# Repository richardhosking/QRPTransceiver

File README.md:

# QRPTransceiver

QRPTransceiver is an HF transceiver project using phasing techniques, surface-mount components, KiCad hardware design files, and Raspberry Pi Pico firmware for control and user interface.

## Overview

The repository combines:

- **hardware design** in KiCad
- **firmware** for Raspberry Pi Pico using PlatformIO/Arduino
- **local oscillator control** using an SI5351
- **front-panel UI** using a rotary encoder, push buttons, and an ILI9341 TFT display

The design is centered on a phasing-based architecture for HF operation and is being developed as an integrated hardware/firmware system.

## Repository Structure

```text
.
├── firmware/
│   ├── src/                # Main firmware application
│   ├── lib/                # Firmware libraries (UI, input, SI5351 control, etc.)
│   ├── include/            # Shared firmware headers
│   ├── test/               # Firmware tests
│   ├── scripts/            # Utility scripts
│   └── platformio.ini      # PlatformIO project file
├── hardware/
│   ├── kicad/
│   │   ├── QRPTransceiver.kicad_pro
│   │   ├── QRPTransceiver.kicad_sch
│   │   ├── QRPTransceiver.kicad_pcb
│   │   ├── QRPTransceiver.pretty/   # Local footprint library
│   │   └── lib_sch/                 # Local symbol library files
│   └── outputs/            # Manufacturing outputs, exports, and generated artifacts
├── docs/
│   ├── architecture.md
│   ├── bringup.md
│   ├── calibration.md
│   ├── firmware-overview.md
│   ├── hardware-overview.md
│   ├── pinout.md
│   └── summaries/          # Summary notes and rework history
├── reference/
│   ├── datasheets/         # Reference component datasheets
│   └── licenses/           # License/reference documents
├── archive/
│   ├── backups/            # Backup zips, cache/rescue files, and *-bak artifacts
│   ├── legacy-kicad/       # Legacy KiCad schematic/netlist files
│   └── temporary/          # Autosave, lock, and temporary design files
└── README.md
```

The repository is now organized so that active firmware lives under `firmware/`, the active KiCad project lives under `hardware/kicad/`, generated hardware outputs live under `hardware/outputs/`, and reference material is stored under `reference/`.

## Main Subsystems

### Hardware
- main transceiver schematic and PCB
- hierarchical sheets for mixer, polyphase, and receiver audio sections
- local symbol and footprint libraries
- manufacturing outputs and design reports

### Firmware
- `firmware/src/main.cpp` as the control entry point
- `firmware/lib/DisplayUI` for the TFT display layer
- `firmware/lib/RotaryInput` for tuning encoder input
- `firmware/lib/PushButtons` for front-panel button handling
- `firmware/lib/SI5351Control` for synthesizer control and band-specific quadrature setup

## Documentation

Project documentation is organized under `docs/`:

- `docs/architecture.md` — overall system architecture
- `docs/bringup.md` — bring-up notes and observations
- `docs/calibration.md` — calibration workflow and notes
- `docs/hardware-overview.md` — hardware design structure and subsystem roles
- `docs/firmware-overview.md` — firmware organization and responsibilities
- `docs/pinout.md` — firmware-visible pin assignments
- `docs/summaries/` — summary notes for key refactors, programming flow, and quadrature correction work

## Current Status

The repository currently contains:
- active KiCad project files under `hardware/kicad/`
- firmware for Pico-based control and display under `firmware/`
- generated outputs under `hardware/outputs/`
- reference materials under `reference/`
- archived legacy, backup, and intermediate design artifacts under `archive/`

As the project evolves, the active KiCad project and PlatformIO firmware remain the primary editable sources in their dedicated subdirectories.

## Toolchain

### Hardware
- KiCad 8 project files are present under `hardware/kicad/`

### Firmware
- PlatformIO
- Arduino framework for Raspberry Pi Pico
- SI5351 library
- Adafruit GFX / ILI9341 display libraries

## Notes

This project is an active mixed-domain design spanning:

- RF/analog circuit design
- phasing-based transceiver architecture
- embedded firmware
- user interface development
- calibration and layout refinement

For architectural details, start with `docs/architecture.md`.

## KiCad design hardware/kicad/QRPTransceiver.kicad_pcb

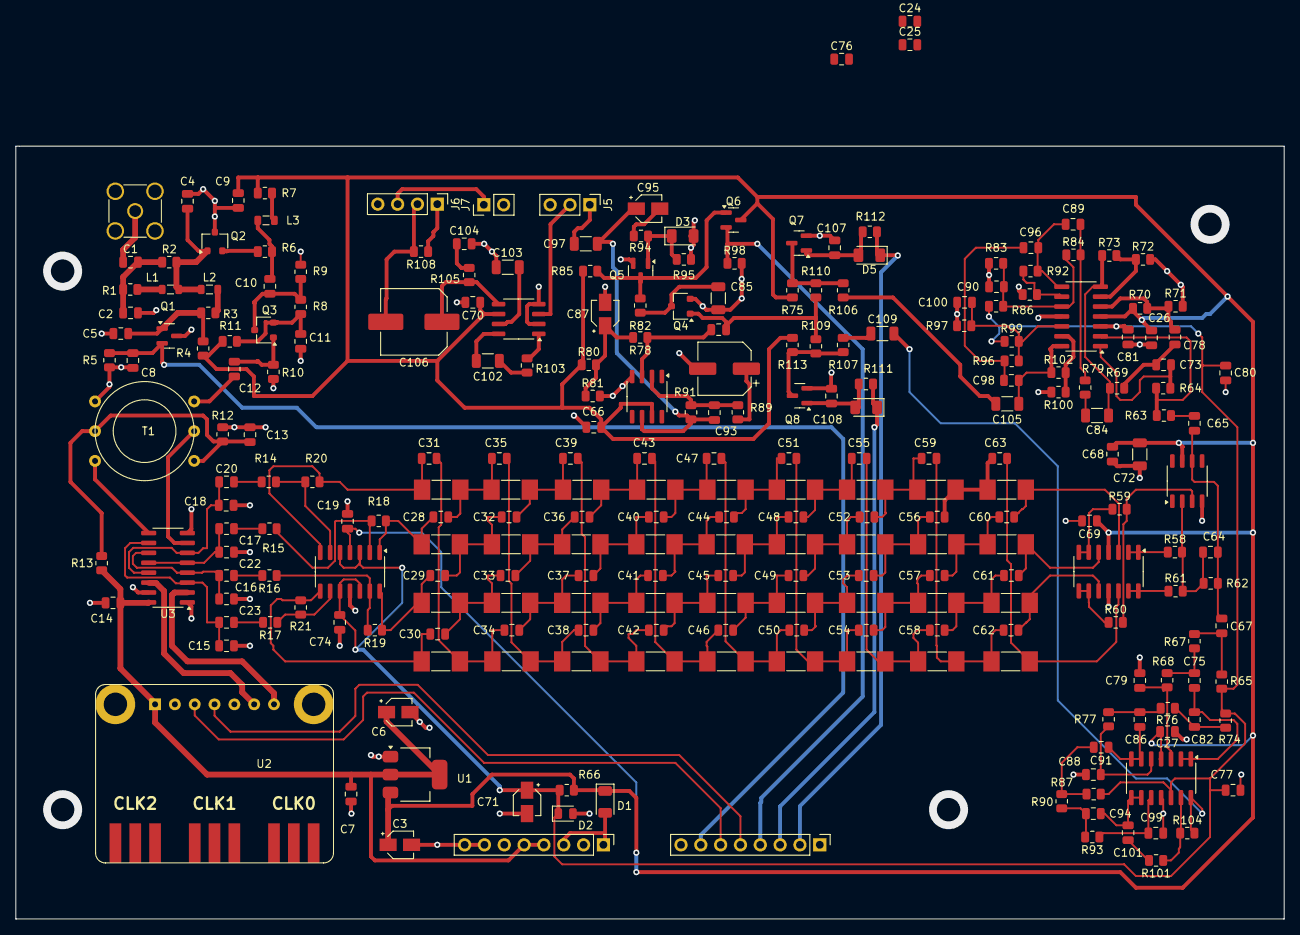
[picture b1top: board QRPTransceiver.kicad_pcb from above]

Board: 2 copper layers, 162.5 x 99.0 mm, 255 parts (0 on the bottom side), 146 nets.

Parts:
C1, C28, C29, C30, C31, C32, C33, C34, C35, C36, C37, C38, C39, C40, C41, C42, C43, C44, C45, C46, C47, C48, C49, C50, C51, C52, C53, C54, C55, C56, C57, C58, C59, C60, C61, C62, C63, C89, C90, C96, C98, C100: 10n; C_0805_2012Metric
C2, C4, C12: 1n; C_0805_2012Metric
C3, C6, C87, C95: 10u; CP_Elec_3x5.3
C5, C7, C8, C9, C10, C11, C13, C14, C19, C24, C25, C26, C27, C65, C66, C67, C68, C69, C70, C73, C74, C76, C77, C78, C80, C81, C83, C101, C107, C108: 100n; C_0805_2012Metric
C15, C16, C17, C18: 470n; C_0805_2012Metric
C20, C21, C22, C23: 220n; C_0805_2012Metric
C64, C79: 220p; C_0805_2012Metric
C71: 47u; CP_Elec_3x5.3
C72, C102, C103: 10u; C_1206_3216Metric
C75, C82, C91, C104: 47n; C_0805_2012Metric
C84, C85, C97, C105, C109: 1u; C_1206_3216Metric
C86, C94: 33n; C_0805_2012Metric
C88, C99: 470p; C_0805_2012Metric
C92: 47u; CP_Elec_6.3x4.9
C93: 33p; C_0805_2012Metric
C106: 220u; C_Elec_8x10.2
D1: IN4001; D_1206_3216Metric
D2: 6V2; D_0805_2012Metric
D3: 1N4142; D_1206_3216Metric
D4, D5: 1N914; D_1206_3216Metric
J1: Data; PinHeader_1x08_P2.54mm_Vertical
J2: Power; PinHeader_1x08_P2.54mm_Vertical
J3: Input; SMA_Amphenol_901-144_Vertical
J5: Audio Gain; PinHeader_1x03_P2.54mm_Vertical
J6: Audio Out; PinHeader_1x04_P2.54mm_Vertical
J7: Speaker; PinHeader_1x02_P2.54mm_Vertical
L1: 100n; L_0805_2012Metric
L2: 1n; L_0805_2012Metric
L3: 500u; L_0805_2012Metric
Q1: VN10N; SOT-23
Q2, Q3: 2SK2394; SC-59
Q4: J177; SC-59
Q5, Q6: 2N3904; SOT-23
Q7, Q8: VN10LF; SOT-23
R1, R3: 47; R_0805_2012Metric
R2: 100; R_0805_2012Metric
R4, R5, R10, R13, R18, R19, R20, R21, R58, R59, R60, R61, R69, R71, R73, R75, R85, R94, R98, R101, R106, R107, R113: 10K; R_0805_2012Metric
R6, R7, R14, R15, R16, R17, R82, R111, R112: 1K; R_0805_2012Metric
R8, R9, R65, R74, R78, R83, R87: 1M; R_0805_2012Metric
R11: 10; R_0805_2012Metric
R12: 6K8; R_0805_2012Metric
R22, R23, R24, R25: 3K3; R_MELF_MMB-0207
R26, R27, R28, R29: 4K7; R_MELF_MMB-0207
R30, R31, R32, R33: 6K8; R_MELF_MMB-0207
R34, R35, R36, R37: 10K; R_MELF_MMB-0207
R38, R39, R40, R41: 15K; R_MELF_MMB-0207
R42, R43, R44, R45: 22K; R_MELF_MMB-0207
R46, R47, R48, R49: 33K; R_MELF_MMB-0207
R50, R51, R52, R53: 47K; R_MELF_MMB-0207
R54, R55, R56, R57: 68K; R_MELF_MMB-0207
R62, R91: 220K; R_0805_2012Metric
R63: 22K; R_0805_2012Metric
R64, R95, R102: 47K; R_0805_2012Metric
R66, R79, R84: 4K7; R_0805_2012Metric
R67, R68, R72: 33K; R_0805_2012Metric
R70, R92: 18K; R_0805_2012Metric
R76, R77, R90, R93: 56K; R_0805_2012Metric
R80, R81, R109, R110: 100K; R_0805_2012Metric
R86, R99: 470K; R_0805_2012Metric
R88, R100: 39K; R_0805_2012Metric
R89, R96: 3K3; R_0805_2012Metric
R97: 390K; R_0805_2012Metric
R103: 1K2; R_0805_2012Metric
R104: 27K; R_0805_2012Metric
R105: 10R; R_0805_2012Metric
R108: 470R; R_0805_2012Metric
T1: Input; T50-2TrifilarTransformer
U1: AP1117-50; SOT-223-3_TabPin2
U2: Si5351Module
U3: FST3253; SOIC-16_3.9x9.9mm_P1.27mm
U4, U5, U7, U8: TS924; SO-14_3.9x8.65mm_P1.27mm
U6, U9: OPA1641; SO-8_3.9x4.9mm_P1.27mm
U10: LM386; SO-8_3.9x4.9mm_P1.27mm

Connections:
+5V: C6.1, C7.1, C14.1, J2.4, J2.5, R13.1, U1.2 (VO), U2.1 (VCC), U3.16 (VCC)
+12V: C3.1, C9.1, C19.1, C24.1, C25.1, C26.1, C27.1, C66.1, C68.1, C69.1, C70.1, C72.1, C76.1, D1.1 (K), Q6.3, R4.2, R7.2, R11.2, R66.1, R70.2, R75.1, R80.1, R85.1, R113.1, U1.3 (VI), U4.4 (V+), U5.4 (V+), U6.7 (V+), U7.4 (V+), U8.4 (V+), U9.7 (V+), U10.6 (V+)
/Sheet6280C94B/AudioAGC: C83.1, Q4.1 (D), R109.1, R110.1
/Sheet62579414/A: C31.2, R20.1, R22.2, U4.7
/Sheet62579414/B: C28.1, C35.2, R22.1, R26.2
/Sheet62579414/C: C32.1, C39.2, R26.1, R30.2
/Sheet62579414/D: C36.1, C43.2, R30.1, R34.2
/Sheet62579414/E: C40.1, C47.2, R34.1, R38.2
/Sheet62579414/F: C44.1, C51.2, R38.1, R42.2
/Sheet62579414/G: C48.1, C55.2, R42.1, R46.2
/Sheet62579414/H: C52.1, C59.2, R46.1, R50.2
/Sheet62579414/J: C56.1, C63.2, R50.1, R54.2
CWMUTE: D4.1 (K), J1.3, R111.1
GND: C2.2, C3.2, C4.2, C5.2, C6.2, C7.2, C8.2, C9.2, C11.2, C13.2, C14.2, C15.2, C16.2, C17.2, C18.2, C19.2, C24.2, C25.2, C26.2, C27.2, C66.2, C68.2, C69.2, C70.2, C71.2, C72.2, C74.2, C76.2, C77.2, C79.1, C80.2, C81.2, C85.2, C87.2, C88.1, C90.2, C92.2, C99.1, C100.2, C103.1, C104.2, C107.2, C108.2, D2.2 (A), D3.2 (A), J1.8, J2.7, J2.8, J3.2 (Ext), J5.3, J6.4, J7.2, Q1.3 (S), Q2.3 (G), Q4.2 (S), Q5.2, Q7.2 (S), Q8.2 (S), R5.2, R9.2, R10.2, R12.2, R71.2, R72.2, R81.2, R83.2, R88.2, R95.2, R97.2, R98.2, R100.2, T1.2 (AB), U1.1 (GND), U2.2 (GND), U3.1 (1~OE), U3.8 (GND), U3.15 (2~OE), U4.11 (V-), U5.11 (V-), U6.4 (V-), U7.11 (V-), U8.11 (V-), U9.4 (V-), U10.2 (-), U10.4 (GND)
Mix0Deg: C18.1, C20.1, U3.6 (1B1), U3.13 (2B4)
Mix90Deg: C17.1, C21.1, U3.5 (1B2), U3.12 (2B3)
Mix180Deg: C16.1, C22.1, U3.4 (1B3), U3.11 (2B2)
Mix270Deg: C15.1, C23.1, U3.3 (1B4), U3.10 (2B1)
unnamed: C1.2, C2.1, R1.1, R2.1
unnamed: C10.1, L3.1, R6.2
unnamed: C20.2, R14.2
unnamed: C21.2, R15.2
unnamed: C22.2, R16.2
unnamed: C23.2, R17.2
unnamed: C28.2, R18.1, R23.2, U4.1
unnamed: C29.1, C32.2, R23.1, R27.2
unnamed: C29.2, R19.1, R24.2, U4.14
unnamed: C30.1, C33.2, R24.1, R28.2
unnamed: C30.2, R21.1, R25.2, U4.8
unnamed: C31.1, C34.2, R25.1, R29.2
unnamed: C33.1, C36.2, R27.1, R31.2
unnamed: C34.1, C37.2, R28.1, R32.2
unnamed: C35.1, C38.2, R29.1, R33.2
unnamed: C37.1, C40.2, R31.1, R35.2
unnamed: C38.1, C41.2, R32.1, R36.2
unnamed: C39.1, C42.2, R33.1, R37.2
unnamed: C41.1, C44.2, R35.1, R39.2
unnamed: C42.1, C45.2, R36.1, R40.2
unnamed: C43.1, C46.2, R37.1, R41.2
unnamed: C45.1, C48.2, R39.1, R43.2
unnamed: C46.1, C49.2, R40.1, R44.2
unnamed: C47.1, C50.2, R41.1, R45.2
unnamed: C49.1, C52.2, R43.1, R47.2
unnamed: C50.1, C53.2, R44.1, R48.2
unnamed: C51.1, C54.2, R45.1, R49.2
unnamed: C53.1, C56.2, R47.1, R51.2
unnamed: C54.1, C57.2, R48.1, R52.2
unnamed: C55.1, C58.2, R49.1, R53.2
unnamed: C57.1, C60.2, R51.1, R55.2
unnamed: C58.1, C61.2, R52.1, R56.2
unnamed: C59.1, C62.2, R53.1, R57.2
unnamed: C65.2, R63.2
unnamed: C67.2, R65.2, R67.1
unnamed: C73.1, R64.1, U8.1
unnamed: C73.2, C78.1, R69.1
unnamed: C75.2, R67.2, R68.2
unnamed: C82.2, R74.2, R76.2
unnamed: C84.1, R69.2, R73.1, U8.7
unnamed: C84.2, R79.2
unnamed: C86.2, R76.1, R77.2
unnamed: C87.1, R78.2, R80.2, R81.1
unnamed: C89.1, C96.1, R92.1, U8.8
unnamed: C89.2, R79.1, R84.2
unnamed: C91.2, R87.2, R90.2
unnamed: C92.1, R89.2
unnamed: C93.2, C95.1, C97.1, R91.1, U9.6
unnamed: C94.2, R90.1, R93.2
unnamed: C95.2, R94.1
unnamed: C96.2, C98.2, R96.2
unnamed: C101.2, R101.2
unnamed: C102.1, U10.8 (GAIN)
unnamed: C102.2, R103.2
unnamed: C104.1, R105.2
unnamed: C105.1, R106.2
unnamed: C98.1, C105.2, R102.1, U8.14
unnamed: C106.1, R105.1, U10.5
unnamed: C109.1, R107.2
unnamed: C109.2, R104.2, U7.14
unnamed: D1.2 (A), J2.1, J2.3
unnamed: D3.1 (K), Q5.1, R94.2, R95.1
unnamed: C108.1, D4.2 (A), Q8.1 (G), R111.2
unnamed: C107.1, D5.2 (A), Q7.1 (G), R112.2
unnamed: C1.1, J3.1 (In)
unnamed: C97.2, J5.1
unnamed: J5.2, U10.3 (+)
unnamed: J6.1, R108.1
unnamed: C106.2, J6.2, R108.2
unnamed: J6.3, J7.1
unnamed: L1.1, R1.2
unnamed: L2.2, R3.2
unnamed: L3.2, R7.1
unnamed: C5.1, Q1.1 (D), R3.1, R4.1
unnamed: Q2.2 (D), R6.1
unnamed: C4.1, L1.2, L2.1, Q2.1 (S), R2.2
unnamed: C11.1, Q3.2 (D), R8.1, R11.1
unnamed: C10.2, Q3.3 (G), R8.2, R9.1
unnamed: C12.1, Q3.1 (S), R10.1
unnamed: C85.1, Q4.3 (G), R82.1
unnamed: Q5.3, Q6.1, R82.2, R85.2
unnamed: Q7.3 (D), R75.2, R106.1, R110.2
unnamed: Q8.3 (D), R107.1, R109.2, R113.2
unnamed: R103.1, U10.1 (GAIN)
unnamed: C12.2, T1.1 (AA)
unnamed: T1.3 (SA), U3.7 (1A)
unnamed: C13.1, R12.1, R13.2, T1.4 (SB), T1.5 (SC)
unnamed: T1.6 (SD), U3.9 (2A)
unnamed: U2.7 (CLK0), U3.2 (S1)
unnamed: U2.6 (CLK1), U3.14 (S0)
unnamed: R15.1, R18.2, U4.2 (-)
unnamed: R14.1, R20.2, U4.6 (-)
unnamed: R17.1, R21.2, U4.9 (-)
unnamed: R16.1, R19.2, U4.13 (-)
unnamed: C60.1, R54.1, U5.3 (+)
unnamed: R58.1, U5.1, U5.2 (-)
unnamed: C61.1, R55.1, U5.5 (+)
unnamed: R59.1, U5.6 (-), U5.7
unnamed: C62.1, R56.1, U5.10 (+)
unnamed: R60.1, U5.8, U5.9 (-)
unnamed: C63.1, R57.1, U5.12 (+)
unnamed: R61.1, U5.13 (-), U5.14
unnamed: R59.2, R60.2, U6.3 (+)
unnamed: C64.1, R58.2, R61.2, R62.1, U6.2 (-)
unnamed: C79.2, R68.1, U7.3 (+)
unnamed: C75.1, C82.1, U7.1, U7.2 (-)
unnamed: C88.2, R77.1, U7.5 (+)
unnamed: C86.1, C91.1, U7.6 (-), U7.7
unnamed: C99.2, R93.1, U7.10 (+)
unnamed: C94.1, C101.1, U7.8, U7.9 (-)
unnamed: R101.1, R104.1, U7.13 (-)
unnamed: R63.1, R64.2, U8.2 (-)
unnamed: C78.2, R70.1, R71.1, U8.5 (+)
unnamed: R72.1, R73.2, U8.6 (-)
unnamed: C90.1, R83.1, R84.1, R86.2, U8.10 (+)
unnamed: R88.1, R92.2, U8.9 (-)
unnamed: C100.1, R96.1, R97.1, R99.2, U8.12 (+)
unnamed: R100.1, R102.2, U8.13 (-)
unnamed: C83.2, R78.1, U9.3 (+)
unnamed: C93.1, R89.1, R91.2, U9.2 (-)
unnamed: C103.2, U10.7 (BYPASS)
PPOut: C64.2, C65.1, C67.1, R62.2, U6.6
RXMUTE: C8.1, J1.7, Q1.2 (G), R5.1
SCL: J1.5, U2.4 (SCL)
SDA: J1.6, U2.3 (SDA)
SMETER: J1.4, Q6.2, R98.1
SSBMUTE: D5.1 (K), J1.2, R112.1
VREF: C71.1, C74.1, C77.1, C80.1, C81.1, D2.1 (K), R65.1, R66.2, R74.1, R86.1, R87.1, R99.1, U4.3 (+), U4.5 (+), U4.10 (+), U4.12 (+), U7.12 (+), U8.3 (+)

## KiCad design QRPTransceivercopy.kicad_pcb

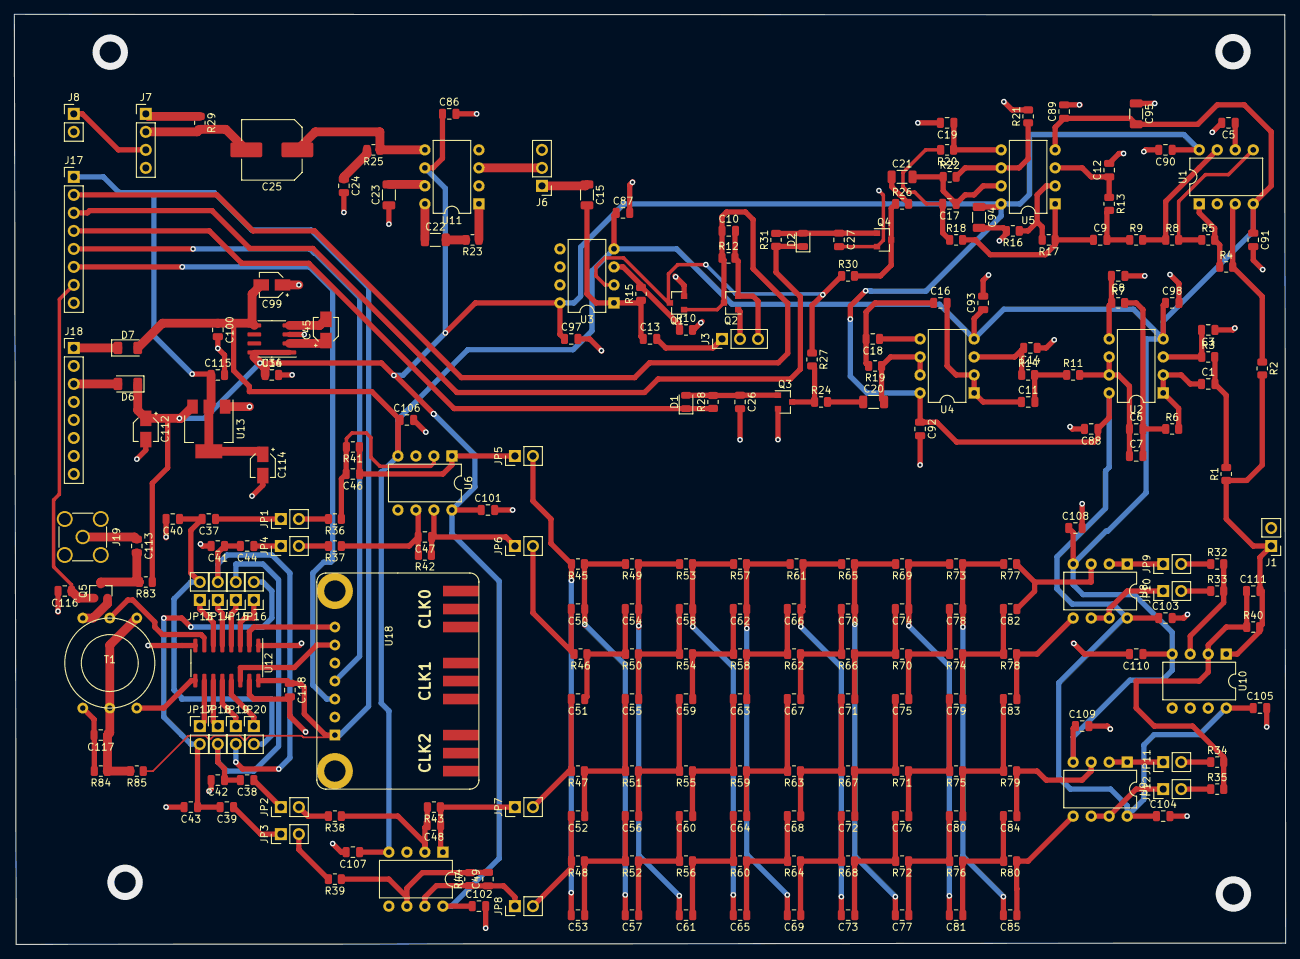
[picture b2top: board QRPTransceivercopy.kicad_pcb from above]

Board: 2 copper layers, 179.3 x 131.2 mm, 243 parts (0 on the bottom side), 148 nets.

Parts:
C1, C24: 47n; C_0805_2012Metric
C3, C8, C14: 1n; C_0805_2012Metric
C5, C9, C12, C17, C19: 18n; C_0805_2012Metric
C6: 33n; C_0805_2012Metric
C7: 3n3; C_0805_2012Metric
C10, C13, C26, C27, C36, C37, C38, C39, C44, C86, C87, C88, C89, C90, C91, C92, C93, C97, C98, C100, C101, C102, C103, C104, C105, C106, C107, C108, C109, C110, C113, C115, C116, C117, C118: 100n; C_0805_2012Metric
C11: 39n; C_0805_2012Metric
C15, C20, C21: 1u; C_1206_3216Metric
C16, C18: 2n2; C_0805_2012Metric
C22, C23, C94, C95: 10u; C_1206_3216Metric
C25: 220u; C_Elec_8x10.2
C40, C41, C42, C43: 470n; C_0805_2012Metric
C45, C99, C112, C114: 10u; CP_Elec_3x5.3
C46, C47, C48, C49, C50, C51, C52, C53, C54, C55, C56, C57, C58, C59, C60, C61, C62, C63, C64, C65, C66, C67, C68, C69, C70, C71, C72, C73, C74, C75, C76, C77, C78, C79, C80, C81, C82, C83, C84, C85, C111: 10n; C_0805_2012Metric
D1, D2: 1N914; D_0805_2012Metric
D6: IN4001; D_1206_3216Metric
D7: 1N4001; D_1206_3216Metric
J1: Audio In; PinHeader_1x02_P2.54mm_Vertical
J3: RF/AGC Gain; PinHeader_1x03_P2.54mm_Vertical
J6: Audio Gain; PinHeader_1x03_P2.54mm_Vertical
J7: Audio Out; PinHeader_1x04_P2.54mm_Vertical
J8: Speaker; PinHeader_1x02_P2.54mm_Vertical
J17: Data; PinHeader_1x08_P2.54mm_Vertical
J18: Power; PinHeader_1x08_P2.54mm_Vertical
J19: Input; SMA_Amphenol_901-144_Vertical
JP1, JP2, JP3, JP4, JP5, JP6, JP7, JP8, JP9, JP10, JP11, JP12, JP13, JP14, JP15, JP16, JP17, JP18, JP19, JP20: Jumper_NO_Small; PinHeader_1x02_P2.54mm_Vertical
Q1, Q3, Q4, Q5: VN10LF; SOT-23
Q2: BCW89; SOT-23
R1, R3, R69, R70, R71, R72: 33K; R_0805_2012Metric
R2, R65, R66, R67, R68: 22K; R_0805_2012Metric
R4: 220K; R_0805_2012Metric
R5, R8, R9, R13, R18, R19, R20, R32, R33, R34, R35, R40, R41, R42, R43, R44, R57, R58, R59, R60, R83, R85: 10K; R_0805_2012Metric
R6, R7, R73, R74, R75, R76: 47K; R_0805_2012Metric
R10, R24, R26: 1K; R_0805_2012Metric
R11, R14: 36K; R_0805_2012Metric
R12: 1k; R_0805_2012Metric
R15: 47k; R_0805_2012Metric
R16, R21: 39K; R_0805_2012Metric
R17, R61, R62, R63, R64: 15K; R_0805_2012Metric
R22: 56K; R_0805_2012Metric
R23: 1K2; R_0805_2012Metric
R25: 10R; R_0805_2012Metric
R27, R30: 100K; R_0805_2012Metric
R28, R31: 120K; R_0805_2012Metric
R29: 470R; R_0805_2012Metric
R36, R37, R38, R39: 100R; R_0805_2012Metric
R45, R46, R47, R48: 3K3; R_0805_2012Metric
R49, R50, R51, R52: 4K7; R_0805_2012Metric
R53, R54, R55, R56, R84: 6K8; R_0805_2012Metric
R77, R78, R79, R80: 68K; R_0805_2012Metric
T1: Input; T50-2TrifilarTransformer
U1, U2, U3, U4, U5, U6, U7, U8, U9, U10: LM4562; DIP-8_W7.62mm
U11: LM386; DIP-8_W7.62mm
U12: FST3253; SOIC-16_3.9x9.9mm_P1.27mm
U13: AP1117-50; SOT-223-3_TabPin2
U14: TC7662Bx0A; SOIC-8_3.9x4.9mm_P1.27mm
U18: Si5351Module

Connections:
+5V: C114.1, C115.1, C118.1, J17.1, R85.1, U12.16, U13.2, U18.1
+12V: C36.1, C86.1, C88.1, C90.1, C92.1, C94.1, C97.1, C101.1, C102.1, C103.1, C104.1, C105.1, C112.1, D6.1, R83.1, U1.8, U2.8, U3.8, U4.8, U5.8, U6.8, U7.8, U8.8, U9.8, U10.8, U11.6, U13.3, U14.1, U14.8
-12V: C87.1, C89.1, C91.1, C93.1, C95.2, C98.1, C99.2, C100.1, C106.1, C107.1, C108.1, C109.1, C110.1, D7.2, U1.4, U2.4, U3.4, U4.4, U5.4, U6.4, U7.4, U8.4, U9.4, U10.4, U14.5
/Sheet6280C94B/AUDIOAGC: Q1.3, R27.1, R30.1, U3.2
/Sheet62579414/A: C53.2, JP5.2, R45.2
/Sheet62579414/B: C50.1, C57.2, R45.1, R49.2
/Sheet62579414/C: C54.1, C61.2, R49.1, R53.2
/Sheet62579414/D: C58.1, C65.2, R53.1, R57.2
/Sheet62579414/E: C62.1, C69.2, R57.1, R61.2
/Sheet62579414/F: C66.1, C73.2, R61.1, R65.2
/Sheet62579414/G: C70.1, C77.2, R65.1, R69.2
/Sheet62579414/H: C74.1, C81.2, R69.1, R73.2
/Sheet62579414/J: C78.1, C85.2, R73.1, R77.2
CWMUTE: D1.1, J17.4, R28.1
GND: C3.1, C5.2, C8.1, C10.2, C12.2, C14.1, C19.2, C23.1, C24.2, C26.2, C27.2, C36.2, C40.2, C41.2, C42.2, C43.2, C86.2, C87.2, C88.2, C89.2, C90.2, C91.2, C92.2, C93.2, C94.2, C95.1, C97.2, C98.2, C99.1, C100.2, C101.2, C102.2, C103.2, C104.2, C105.2, C106.2, C107.2, C108.2, C109.2, C110.2, C112.2, C114.2, C115.2, C116.2, C117.2, C118.2, J1.2, J3.3, J6.3, J7.4, J8.2, J17.8, J18.7, J18.8, J19.2, Q1.2, Q2.2, Q3.2, Q4.2, R10.2, R12.2, R16.2, R21.2, R84.2, T1.2, U1.2, U6.3, U6.5, U7.3, U7.5, U11.2, U11.4, U12.1, U12.8, U12.15, U13.1, U14.3, U18.2
Mix0Deg: C37.2, C40.1, JP13.2, JP20.2
Mix90Deg: C41.1, C44.2, JP14.2, JP19.2
Mix180Deg: C38.2, C42.1, JP15.2, JP18.2
Mix270Deg: C39.2, C43.1, JP16.2, JP17.2
unnamed: C1.1, R6.2, U2.1, U2.2
unnamed: C1.2, R1.2, R3.2
unnamed: C3.2, R3.1, U2.3
unnamed: C5.1, U1.6
unnamed: C6.1, C7.1, R11.2, U2.6, U2.7
unnamed: C6.2, C7.2, R6.1, R7.2
unnamed: C8.2, R7.1, U2.5
unnamed: C9.1, R17.1, R18.2, U5.1
unnamed: C9.2, R9.1, R13.2
unnamed: C11.1, C16.2, U4.1, U4.2
unnamed: C11.2, R11.1, R14.2
unnamed: C12.1, R13.1, U5.3
unnamed: C13.1, C15.2, R15.1, U3.1
unnamed: C13.2, J3.1
unnamed: C14.2, R14.1, U4.3
unnamed: C15.1, J6.1
unnamed: C16.1, C18.2, R19.2
unnamed: C17.1, C21.2, R22.1, U5.7
unnamed: C17.2, R18.1, R20.2
unnamed: C18.1, U4.5
unnamed: C19.1, R20.1, U5.5
unnamed: C20.1, R24.2
unnamed: C20.2, R19.1, U4.6, U4.7
unnamed: C21.1, R26.2
unnamed: C22.1, U11.8
unnamed: C22.2, R23.2
unnamed: C23.2, U11.7
unnamed: C24.1, R25.2
unnamed: C25.1, R25.1, U11.5
unnamed: C25.2, J7.2, R29.2
unnamed: C26.1, D1.2, Q3.1, R28.2
unnamed: C27.1, D2.2, Q4.1, R31.2
unnamed: C37.1, JP1.1
unnamed: C38.1, JP2.1
unnamed: C39.1, JP3.1
unnamed: C44.1, JP4.1
unnamed: C45.1, U14.2
unnamed: C45.2, U14.4
unnamed: C46.1, JP5.1, R41.1, U6.1
unnamed: C46.2, R36.1, R41.2, U6.2
unnamed: C47.1, JP6.1, R42.1, U6.7
unnamed: C47.2, R37.1, R42.2, U6.6
unnamed: C48.1, JP7.1, R43.1, U7.1
unnamed: C48.2, R38.1, R43.2, U7.2
unnamed: C49.1, JP8.1, R44.1, U7.7
unnamed: C49.2, R39.1, R44.2, U7.6
unnamed: C50.2, JP6.2, R46.2
unnamed: C51.1, C54.2, R46.1, R50.2
unnamed: C51.2, JP7.2, R47.2
unnamed: C52.1, C55.2, R47.1, R51.2
unnamed: C52.2, JP8.2, R48.2
unnamed: C53.1, C56.2, R48.1, R52.2
unnamed: C55.1, C58.2, R50.1, R54.2
unnamed: C56.1, C59.2, R51.1, R55.2
unnamed: C57.1, C60.2, R52.1, R56.2
unnamed: C59.1, C62.2, R54.1, R58.2
unnamed: C60.1, C63.2, R55.1, R59.2
unnamed: C61.1, C64.2, R56.1, R60.2
unnamed: C63.1, C66.2, R58.1, R62.2
unnamed: C64.1, C67.2, R59.1, R63.2
unnamed: C65.1, C68.2, R60.1, R64.2
unnamed: C67.1, C70.2, R62.1, R66.2
unnamed: C68.1, C71.2, R63.1, R67.2
unnamed: C69.1, C72.2, R64.1, R68.2
unnamed: C71.1, C74.2, R66.1, R70.2
unnamed: C72.1, C75.2, R67.1, R71.2
unnamed: C73.1, C76.2, R68.1, R72.2
unnamed: C75.1, C78.2, R70.1, R74.2
unnamed: C76.1, C79.2, R71.1, R75.2
unnamed: C77.1, C80.2, R72.1, R76.2
unnamed: C79.1, C82.2, R74.1, R78.2
unnamed: C80.1, C83.2, R75.1, R79.2
unnamed: C81.1, C84.2, R76.1, R80.2
unnamed: C82.1, R77.1, U8.3
unnamed: C83.1, R78.1, U8.5
unnamed: C84.1, R79.1, U9.3
unnamed: C85.1, R80.1, U9.5
unnamed: C111.1, R34.2, R35.2, R40.1, U10.2
unnamed: C113.1, J19.1
unnamed: C113.2, Q5.3, R83.2
unnamed: C117.1, R84.1, R85.2, T1.4, T1.5
unnamed: D6.2, J18.3
unnamed: D7.1, J18.1
unnamed: J3.2, Q2.1
unnamed: J6.2, U11.3
unnamed: J7.1, R29.1
unnamed: J7.3, J8.1
unnamed: JP1.2, R36.2
unnamed: JP2.2, R38.2
unnamed: JP3.2, R39.2
unnamed: JP4.2, R37.2
unnamed: JP9.1, U8.1, U8.2
unnamed: JP9.2, R32.1
unnamed: JP10.1, U8.6, U8.7
unnamed: JP10.2, R33.1
unnamed: JP11.1, U9.1, U9.2
unnamed: JP11.2, R34.1
unnamed: JP12.1, U9.6, U9.7
unnamed: JP12.2, R35.1
unnamed: JP13.1, U12.6
unnamed: JP14.1, U12.5
unnamed: JP15.1, U12.4
unnamed: JP16.1, U12.3
unnamed: JP17.1, U12.10
unnamed: JP18.1, U12.11
unnamed: JP19.1, U12.12
unnamed: JP20.1, U12.13
unnamed: Q3.3, R24.1, R27.2
unnamed: Q4.3, R26.1, R30.2
unnamed: Q5.2, T1.1
unnamed: R2.1, R4.2, U1.3
unnamed: R4.1, R5.2, U1.1
unnamed: R5.1, R8.2, U1.5
unnamed: R8.1, R9.2, U1.7
unnamed: R10.1, R15.2, U3.3
unnamed: R16.1, R17.2, U5.2
unnamed: R21.1, R22.2, U5.6
unnamed: R23.1, U11.1
unnamed: R32.2, R33.2, U10.3
unnamed: T1.3, U12.7
unnamed: T1.6, U12.9
unnamed: U12.2, U18.7
unnamed: U12.14, U18.6
PPOut: C111.2, J1.1, R1.1, R2.2, R40.2, U10.1
PTT: C116.1, J17.7, Q5.1
SCL: J17.5, U18.4
SDA: J17.6, U18.3
SMETER: C10.1, J17.2, Q1.1, Q2.3, R12.1
SSBMUTE: D2.1, J17.3, R31.1

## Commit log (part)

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2026-04-22 Add files via upload
    Receiver board KICAD files
2026-04-22 Revise license details and add GPL-3.0 notice
    Updated license information to clarify the repository contains both software and hardware documentation, and specified the licensing for software/firmware under GPL-3.0-or-later.
2026-04-22 Add hardware design files licensing information
2026-04-22 Add GPL-3.0-or-later license file
    Add the GNU General Public License version 3.0 text.
2026-04-22 Add CERN-OHL-S-2.0 license file
    Added CERN Open Hardware Licence Version 2 - Strongly Reciprocal text.
2026-04-30 Add QRPTransceiverV3 software project with SI5351 updates and settings persistence
2026-05-16 Add architecture, hardware overview, and firmware overview documentation and update README
2026-05-16 Add bring-up, calibration, and pinout documentation and expand .gitignore for KiCad and PlatformIO artifacts
2026-05-16 Initial plan
2026-05-16 docs: move summary notes into docs/summaries
    Agent-Logs-Url: https://github.com/richardhosking/QRPTransceiver/sessions/31ed3dec-8c33-4438-bae4-cfb35b52de56
2026-05-16 chore: archive legacy and backup root files
    Agent-Logs-Url: https://github.com/richardhosking/QRPTransceiver/sessions/2329a8e4-cee6-4c88-bb25-dfe96806a3fa
2026-05-16 Reorganize outputs and reference materials into hardware/outputs and reference
2026-05-16 Move PlatformIO firmware project into firmware directory
2026-05-16 Move KiCad project files into hardware/kicad
2026-05-16 Recover mixer in Kicad Schematic
2026-05-17 added transmit and receive board control logic
2026-05-23 Add power button behavior and power latch documentation
2026-05-23 Power cicuit in KICAD
